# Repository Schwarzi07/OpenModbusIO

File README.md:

# OpenModbusIO
Hardware and software for Mobus based remote IO

# Goal
The goal of this project is to create open source IO for Modbus TCP or Modbus RTU. This repository will hold the source code and the PCB design files for this project. 

# Software
Currnetly the software is written in C++ on the Arduino platform via Visual Studio Code and PlatformIO. My plans are to switch to an RTOS when the hardware expands.

# Hardware
The hardware is curently based on Arduino and is using the Arduino Ethernet shield with the Wiznet w5500 Ethernet controller.
I design the PCBs in KiCad and will limit myself to two layers to keep costs low and enable DIY PCB fabrication using CNC milling or other methods.

# Current status
Currently I have basic software and a shield for an Arduino UNO.

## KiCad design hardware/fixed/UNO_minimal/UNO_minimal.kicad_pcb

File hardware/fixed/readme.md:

# General
This is the folder for all hardware designs which arent designed to be expanded and to stay fixed like they currntly are.

# UNO_minimal

This is a prototype for a minimal configuration in form of a shield for the Arduino UNO.
It has 4 Inputs, 2 0-5V inputs and 2 NPN outputs. It doesnt have isolation for the inputs.

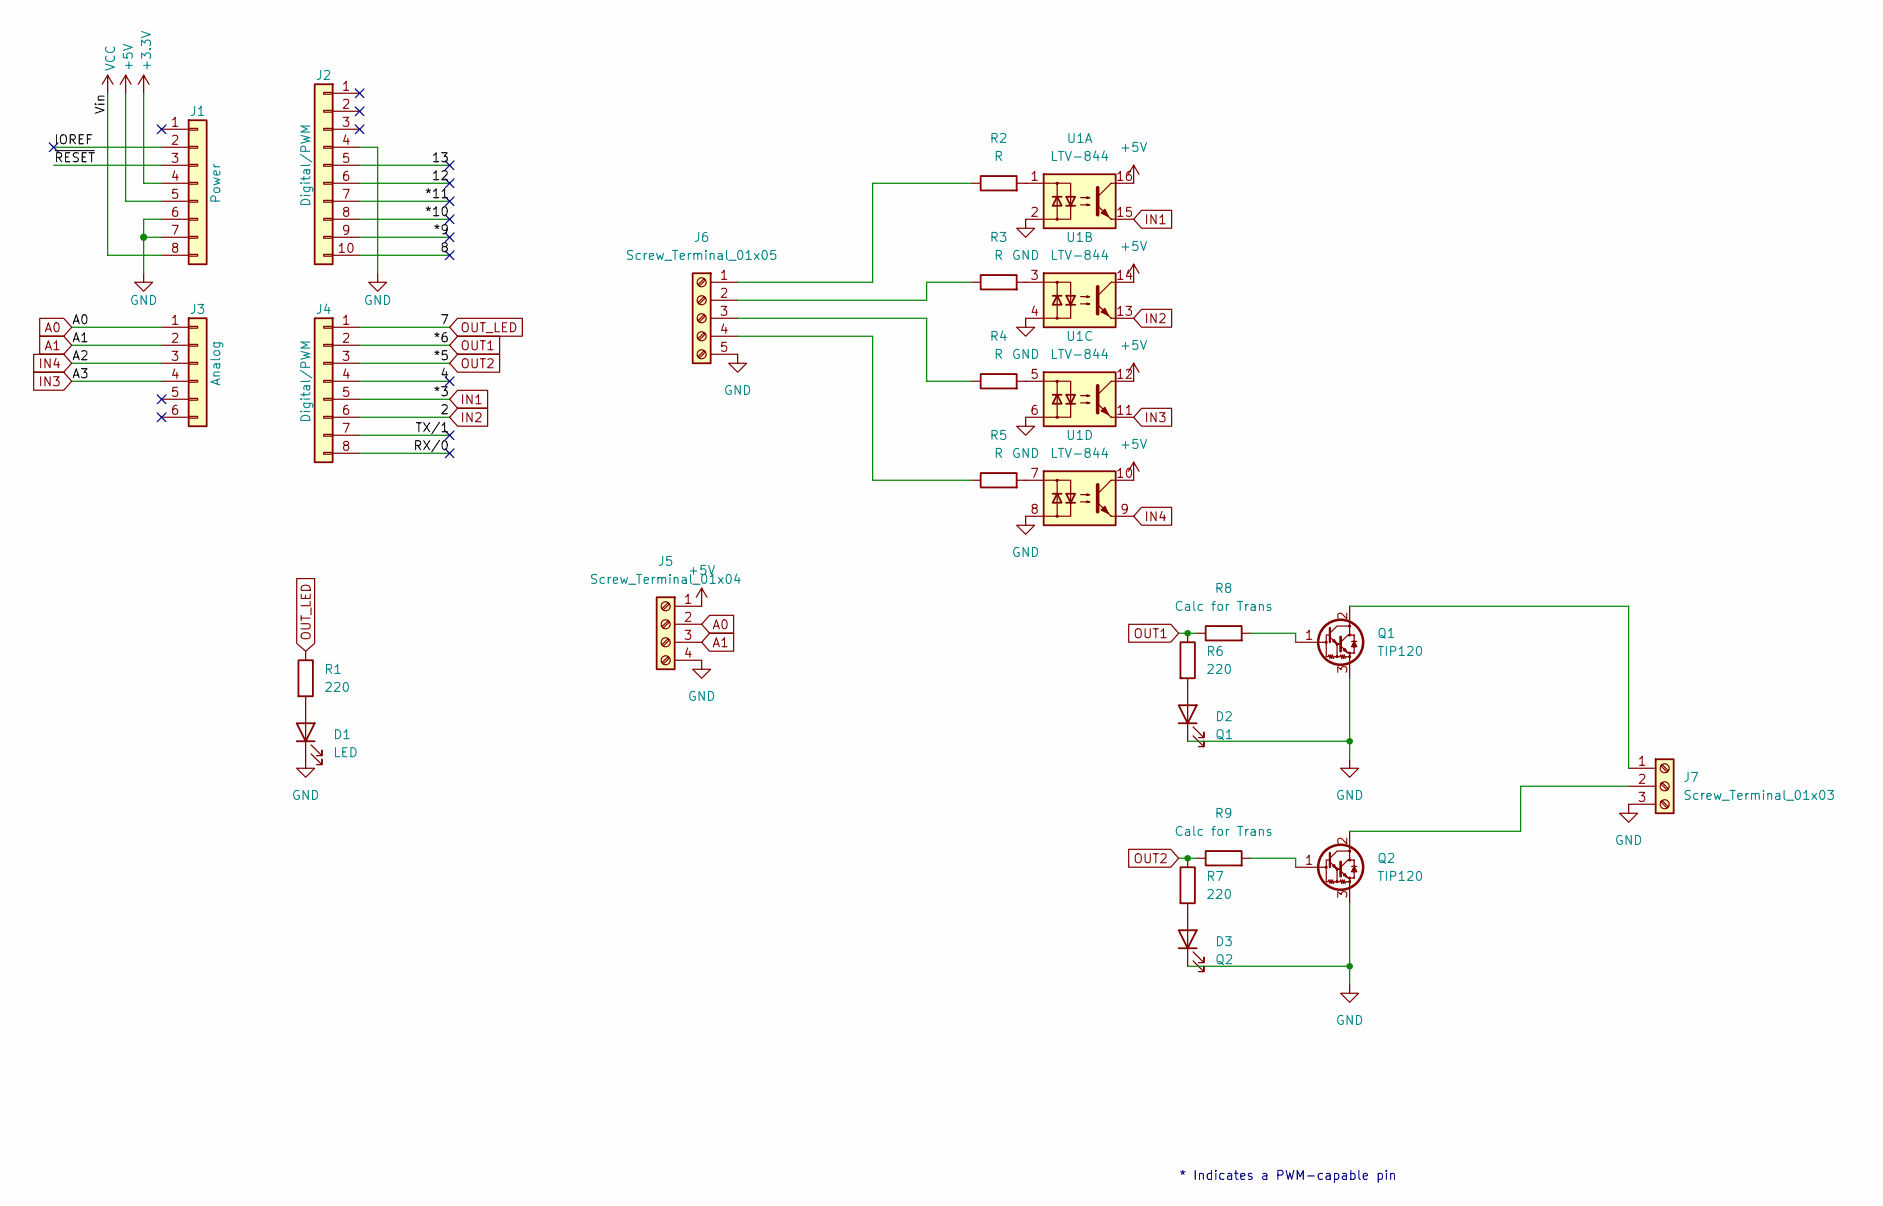
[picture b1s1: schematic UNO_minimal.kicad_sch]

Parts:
D1: LED; LED_D3.0mm
D2: Q1; LED_D3.0mm
D3: Q2; LED_D3.0mm
J1: Power; PinSocket_1x08_P2.54mm_Vertical
J2: Digital/PWM; PinSocket_1x10_P2.54mm_Vertical
J3: Analog; PinSocket_1x06_P2.54mm_Vertical
J4: Digital/PWM; PinSocket_1x08_P2.54mm_Vertical
J5: Screw_Terminal_01x04; TerminalBlock_WAGO_236-104_1x04_P5.00mm_45Degree
J6: Screw_Terminal_01x05; TerminalBlock_WAGO_236-105_1x05_P5.00mm_45Degree
J7: Screw_Terminal_01x03; TerminalBlock_WAGO_236-103_1x03_P5.00mm_45Degree
Q1, Q2: TIP120; TO-220-3_Vertical
R1, R6, R7: 220; R_Axial_DIN0204_L3.6mm_D1.6mm_P5.08mm_Vertical
R2, R3, R4, R5: R; R_Axial_DIN0204_L3.6mm_D1.6mm_P5.08mm_Vertical
R8, R9: Calc for Trans; R_Axial_DIN0204_L3.6mm_D1.6mm_P5.08mm_Vertical
U1: LTV-844; DIP-16_W7.62mm

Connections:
+3V3: J1.4
+5V: J1.5, J5.1, U1.10, U1.12, U1.14, U1.16
/4: J4.4
/8: J2.10
/12: J2.6
/13: J2.5
/*9: J2.9
/*10: J2.8
/*11: J2.7
/IOREF: J1.2
/RX/0: J4.8
/TX/1: J4.7
/~RESET: J1.3
A0: J3.1, J5.2
A1: J3.2, J5.3
GND: D1.1 (K), D2.1 (K), D3.1 (K), J1.6, J1.7, J2.4, J5.4, J6.5, J7.3, Q1.3 (E), Q2.3 (E), U1.2, U1.4, U1.6, U1.8
IN1: J4.5, U1.15
IN2: J4.6, U1.13
IN3: J3.4, U1.11
IN4: J3.3, U1.9
unnamed: D1.2 (A), R1.2
unnamed: D2.2 (A), R6.2
unnamed: D3.2 (A), R7.2
unnamed: J6.1, R2.1
unnamed: J6.2, R3.1
unnamed: J6.3, R4.1
unnamed: J6.4, R5.1
unnamed: J7.1, Q1.2 (C)
unnamed: J7.2, Q2.2 (C)
unnamed: Q1.1 (B), R8.2
unnamed: Q2.1 (B), R9.2
unnamed: R2.2, U1.1
unnamed: R3.2, U1.3
unnamed: R4.2, U1.5
unnamed: R5.2, U1.7
OUT1: J4.2, R6.1, R8.1
OUT2: J4.3, R7.1, R9.1
OUT_LED: J4.1, R1.1
VCC: J1.8

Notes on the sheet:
* Indicates a PWM-capable pin

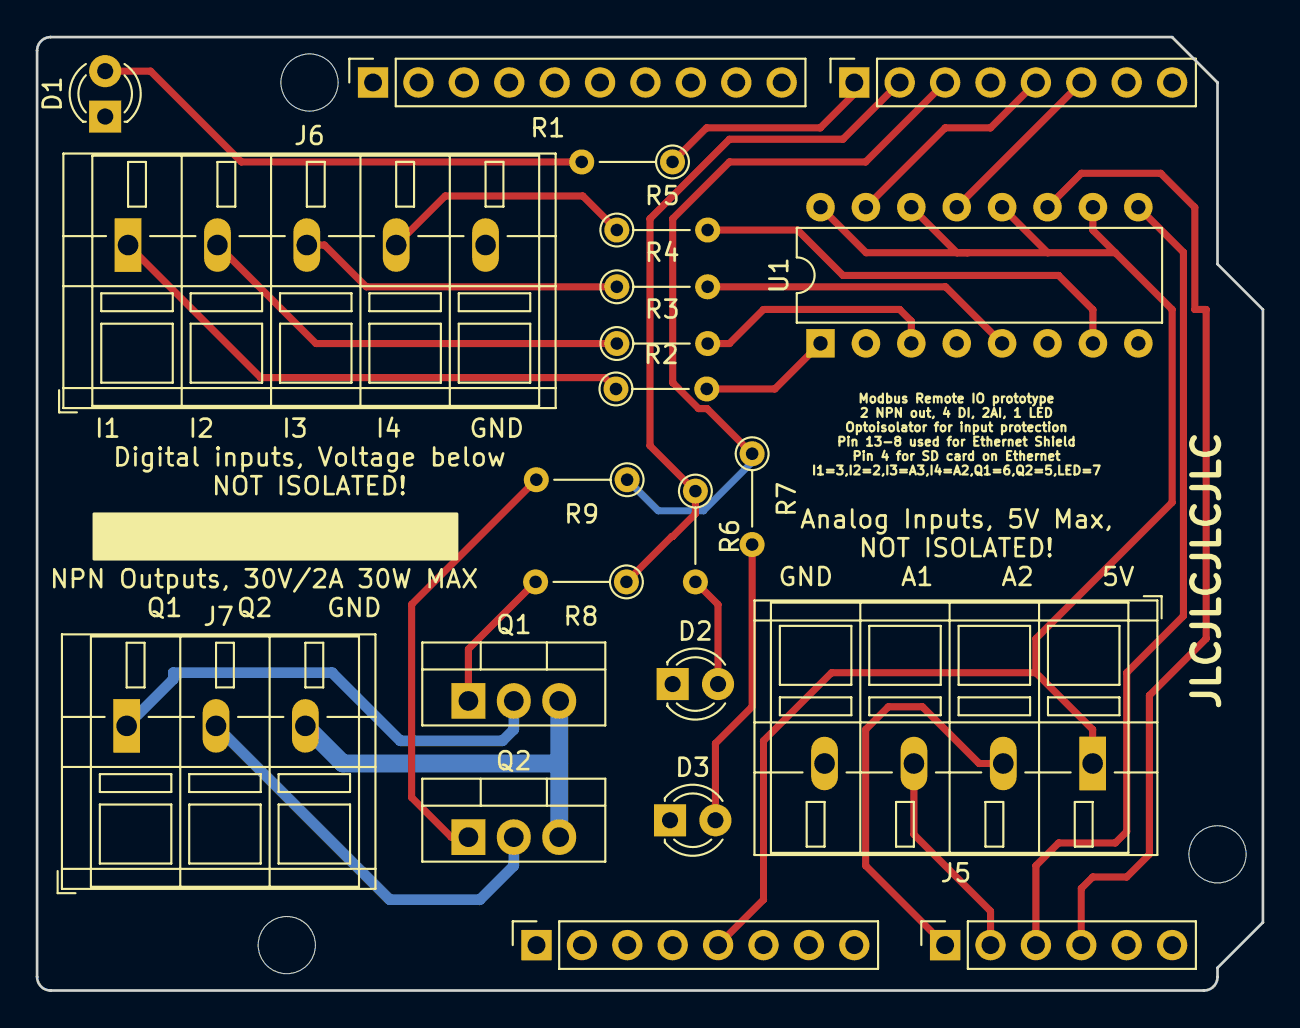
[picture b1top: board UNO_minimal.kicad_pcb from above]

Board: 2 copper layers, 68.6 x 53.3 mm, 25 parts (0 on the bottom side), 26 nets.

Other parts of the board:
MH1, MH2, MH4: MountingHole_3.2mm

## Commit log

2023-07-21 Update README.md
    Added README.md
2023-07-21 added files from local storage to github
2023-07-21 Revert "added files from local storage to github"
    This reverts commit 45506ca0ecf017dd25e77392b1a3004c5c51514a.
2023-07-21 add files from local storage
2023-07-21 added hardware readme
2023-07-21 added readme files
2023-07-21 new software for UNO_minimal board
2023-07-21 converted to kicad 7.0
